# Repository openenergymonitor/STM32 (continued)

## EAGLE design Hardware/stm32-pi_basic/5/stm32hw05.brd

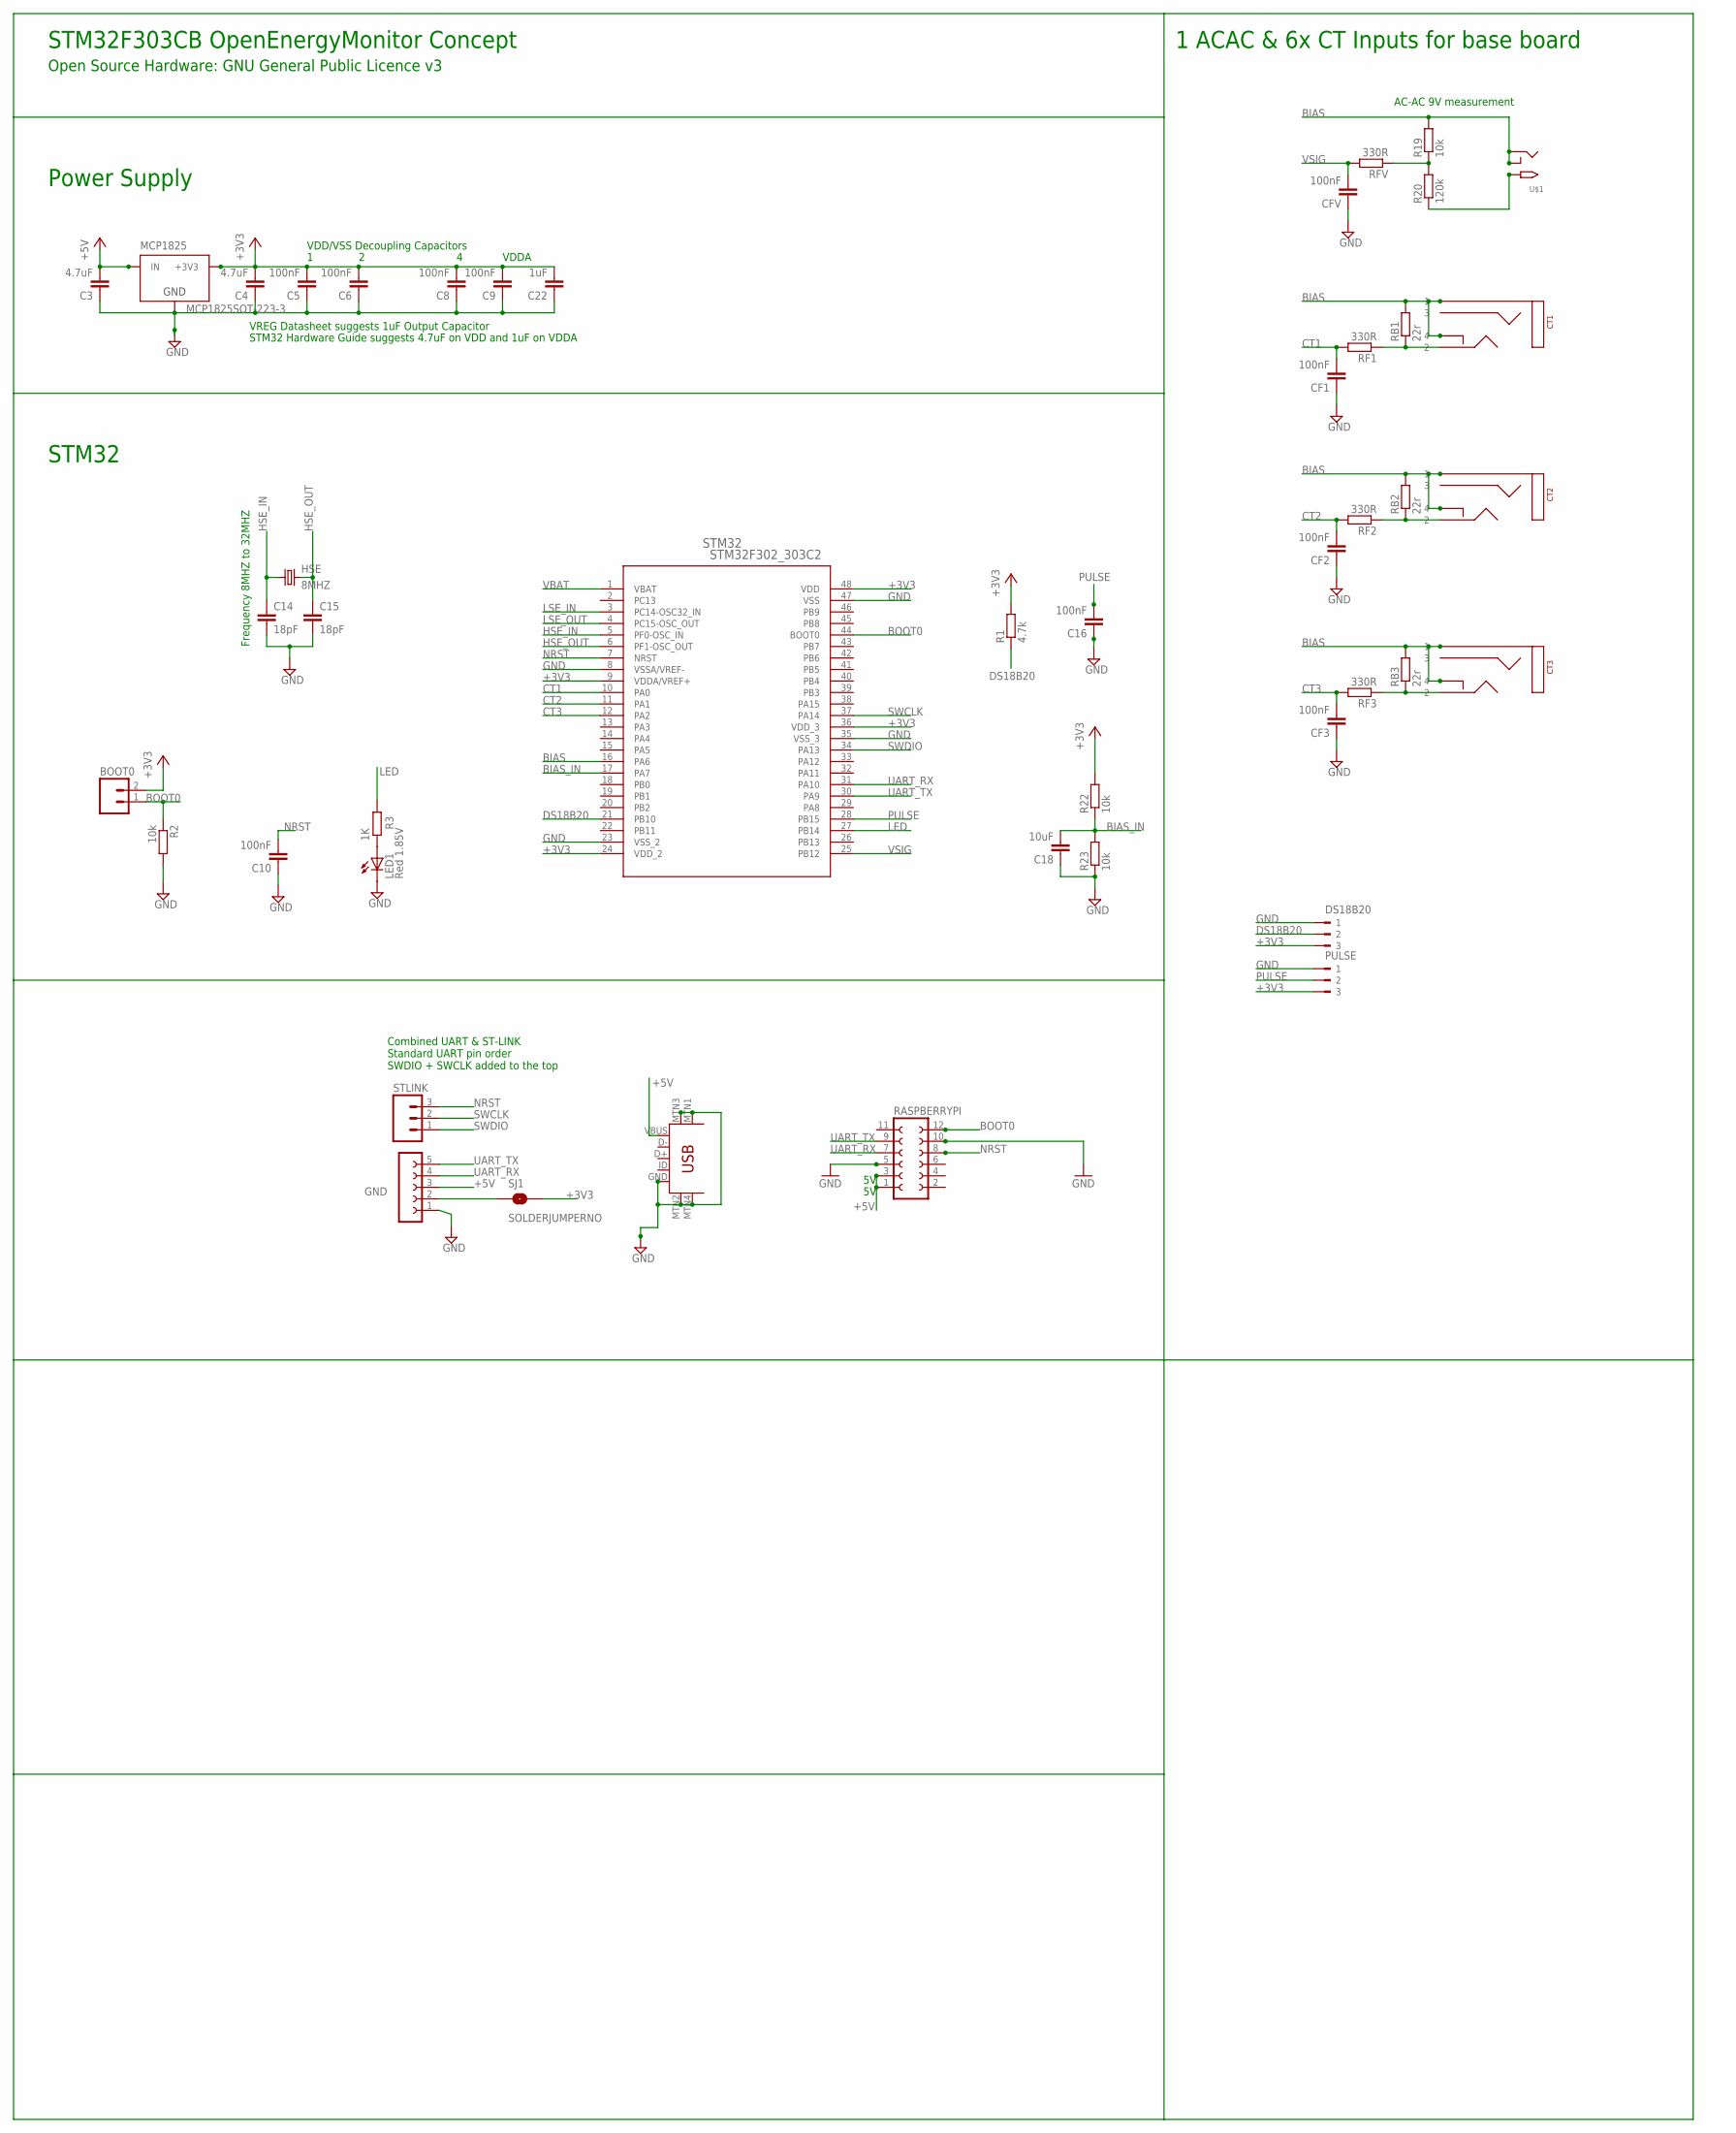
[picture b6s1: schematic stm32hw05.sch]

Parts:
BOOT0: M02PTH; 1X02
C3, C4: 4.7uF; C0603
C5, C6, C8, C9, C10, C16: 100nF; C0603
C14, C15: 18pF; C0603
C18: 10uF; C0603
C22: 1uF; C0603
CF1, CF2, CF3: 100nF; C0603
CFV: 100nF; C0603
CT1, CT2, CT3: STEREO_SMD; STEREO_SMT
DS18B20: 180-3
GND: UART; FE05-1
HSE: 8MHZ; CTS406
LED1: Red 1.85V; CHIP-LED0805
MCP1825: MCP1825SOT-223-3; SOT-223
PULSE: 180-3
R1: 4.7k; R0603
R2, R19, R22, R23: 10k; R0603
R3: 1K; R0603
R20: 120k; R0603
RASPBERRYPI: FE06-2
RB1, RB2, RB3: 22r; R0603
RF1, RF2, RF3: 330R; R0603
RFV: 330R; R0603
SJ1: SOLDERJUMPERNO; SJ_2S-NO
STLINK: M03PTH; 1X03
STM32: STM32F302_303C2; LQFP48-7X7MM
U$1: 2.1MMJACKSMT; DCJACK_2MM_SMT
U$10: USB-MINIB-5PIN; USB-MINIB-CISECO

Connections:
+3V3: BOOT0.2, C4.2, C5.2, C6.2, C8.2, C9.2, C22.2, DS18B20.3, MCP1825.3 (+3V3), PULSE.3, R1.2, R22.2, SJ1.2, STM32.9 (VDDA/VREF+), STM32.24 (VDD_2), STM32.36 (VDD_3), STM32.48 (VDD)
+5V: C3.2, GND.3, MCP1825.1 (IN), RASPBERRYPI.1, RASPBERRYPI.3, U$10.VBUS
AC: R20.1, U$1.PWR2 (TIP)
ADC0: R19.1, R20.2, RFV.1
BIAS: CT1.P$1 (1), CT1.P$4 (4), CT2.P$1 (1), CT2.P$4 (4), CT3.P$1 (1), CT3.P$4 (4), R19.2, RB1.2, RB2.2, RB3.2, STM32.16 (PA6), U$1.GND (RING), U$1.GNDBREAK (RING_SW)
BIAS_IN: C18.2, R22.1, R23.2, STM32.17 (PA7)
BOOT0: BOOT0.1, R2.1, RASPBERRYPI.12, STM32.44 (BOOT0)
CT1: CF1.2, RF1.2, STM32.10 (PA0)
CT2: CF2.2, RF2.2, STM32.11 (PA1)
CT3: CF3.2, RF3.2, STM32.12 (PA2)
DS18B20: DS18B20.2, R1.1, STM32.21 (PB10)
GND: C3.1, C4.1, C5.1, C6.1, C8.1, C9.1, C10.1, C14.2, C15.2, C16.1, C18.1, C22.1, CF1.1, CF2.1, CF3.1, CFV.1, DS18B20.1, GND.1, LED1.C, MCP1825.2 (GND), PULSE.1, R2.2, R23.1, RASPBERRYPI.5, RASPBERRYPI.10, STM32.8 (VSSA/VREF-), STM32.23 (VSS_2), STM32.35 (VSS_3), STM32.47 (VSS), U$10.GND, U$10.MTN1 (MTN2), U$10.MTN2 (MTN3), U$10.MTN3 (MTN1), U$10.MTN4
HSE_IN: C14.1, HSE.1, STM32.5 (PF0-OSC_IN)
HSE_OUT: C15.1, HSE.3 (2), STM32.6 (PF1-OSC_OUT)
LED: R3.2, STM32.27 (PB14)
LSE_IN: STM32.3 (PC14-OSC32_IN)
LSE_OUT: STM32.4 (PC15-OSC_OUT)
unnamed: GND.2, SJ1.1
unnamed: CT1.P$2 (2), RB1.1, RF1.1
unnamed: CT2.P$2 (2), RB2.1, RF2.1
unnamed: CT3.P$2 (2), RB3.1, RF3.1
unnamed: LED1.A, R3.1
NRST: C10.2, RASPBERRYPI.8, STLINK.3, STM32.7 (NRST)
PULSE: C16.2, PULSE.2, STM32.28 (PB15)
SWCLK: STLINK.2, STM32.37 (PA14)
SWDIO: STLINK.1, STM32.34 (PA13)
UART_RX: GND.4, RASPBERRYPI.7, STM32.31 (PA10)
UART_TX: GND.5, RASPBERRYPI.9, STM32.30 (PA9)
VBAT: STM32.1 (VBAT)
VSIG: CFV.2, RFV.2, STM32.25 (PB12)

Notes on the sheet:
VDD/VSS Decoupling Capacitors
VDDA
VREG Datasheet suggests 1uF Output Capacitor
STM32 Hardware Guide suggests 4.7uF on VDD and 1uF on VDDA
Combined UART & ST-LINK Standard UART pin order SWDIO + SWCLK added to the top
AC-AC 9V measurement
1 ACAC & 6x CT Inputs for base board
STM32F303CB OpenEnergyMonitor Concept
Power Supply
STM32
Open Source Hardware: GNU General Public Licence v3
Frequency 8MHZ to 32MHZ

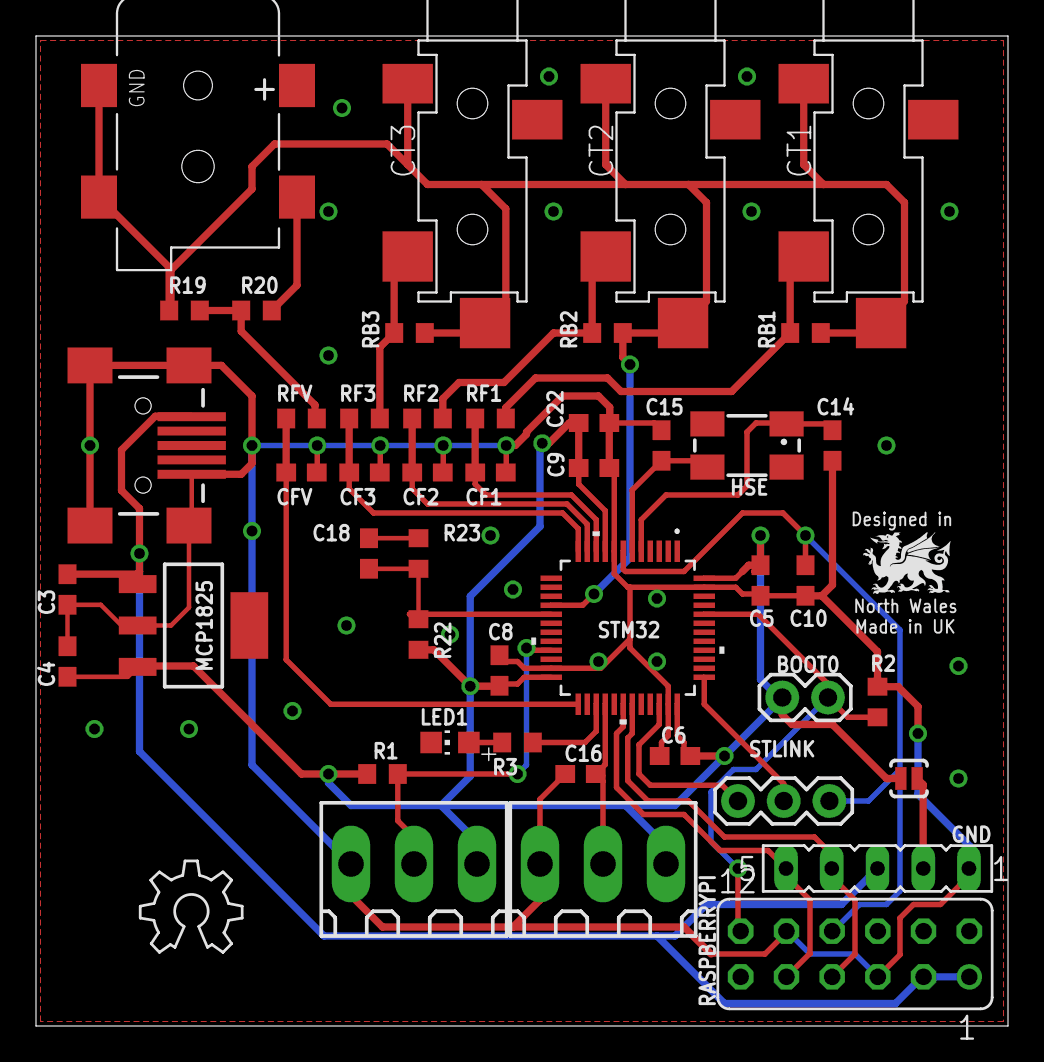
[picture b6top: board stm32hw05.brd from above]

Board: 2 copper layers, 54.0 x 55.0 mm, 47 parts (0 on the bottom side), 27 nets.

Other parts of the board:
LOGO1: OSHW_LOGO_6MILX0200-NT; OSHW_6X200_NOTEXT

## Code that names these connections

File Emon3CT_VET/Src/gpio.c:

/**
  ******************************************************************************
  * File Name          : gpio.c
  * Description        : This file provides code for the configuration
  *                      of all used GPIO pins.
  ******************************************************************************
  ** This notice applies to any and all portions of this file
  * that are not between comment pairs USER CODE BEGIN and
  * USER CODE END. Other portions of this file, whether 
  * inserted by the user or by software development tools
  * are owned by their respective copyright owners.
  *
  * COPYRIGHT(c) 2020 STMicroelectronics
  *
  * Redistribution and use in source and binary forms, with or without modification,
  * are permitted provided that the following conditions are met:
  *   1. Redistributions of source code must retain the above copyright notice,
  *      this list of conditions and the following disclaimer.
  *   2. Redistributions in binary form must reproduce the above copyright notice,
  *      this list of conditions and the following disclaimer in the documentation
  *      and/or other materials provided with the distribution.
  *   3. Neither the name of STMicroelectronics nor the names of its contributors
  *      may be used to endorse or promote products derived from this software
  *      without specific prior written permission.
  *
  * THIS SOFTWARE IS PROVIDED BY THE COPYRIGHT HOLDERS AND CONTRIBUTORS "AS IS"
  * AND ANY EXPRESS OR IMPLIED WARRANTIES, INCLUDING, BUT NOT LIMITED TO, THE
  * IMPLIED WARRANTIES OF MERCHANTABILITY AND FITNESS FOR A PARTICULAR PURPOSE ARE
  * DISCLAIMED. IN NO EVENT SHALL THE COPYRIGHT HOLDER OR CONTRIBUTORS BE LIABLE
  * FOR ANY DIRECT, INDIRECT, INCIDENTAL, SPECIAL, EXEMPLARY, OR CONSEQUENTIAL
  * DAMAGES (INCLUDING, BUT NOT LIMITED TO, PROCUREMENT OF SUBSTITUTE GOODS OR
  * SERVICES; LOSS OF USE, DATA, OR PROFITS; OR BUSINESS INTERRUPTION) HOWEVER
  * CAUSED AND ON ANY THEORY OF LIABILITY, WHETHER IN CONTRACT, STRICT LIABILITY,
  * OR TORT (INCLUDING NEGLIGENCE OR OTHERWISE) ARISING IN ANY WAY OUT OF THE USE
  * OF THIS SOFTWARE, EVEN IF ADVISED OF THE POSSIBILITY OF SUCH DAMAGE.
  *
  ******************************************************************************
  */

/* Includes ------------------------------------------------------------------*/
#include "gpio.h"
/* USER CODE BEGIN 0 */

/* USER CODE END 0 */

/*----------------------------------------------------------------------------*/
/* Configure GPIO                                                             */
/*----------------------------------------------------------------------------*/
/* USER CODE BEGIN 1 */

/* USER CODE END 1 */

/** Configure pins as 
        * Analog 
        * Input 
        * Output
        * EVENT_OUT
        * EXTI
        * Free pins are configured automatically as Analog (this feature is enabled through 
        * the Code Generation settings)
*/
void MX_GPIO_Init(void)
{

  GPIO_InitTypeDef GPIO_InitStruct;

  /* GPIO Ports Clock Enable */
  __HAL_RCC_GPIOE_CLK_ENABLE();
  __HAL_RCC_GPIOC_CLK_ENABLE();
  __HAL_RCC_GPIOF_CLK_ENABLE();
  __HAL_RCC_GPIOA_CLK_ENABLE();
  __HAL_RCC_GPIOB_CLK_ENABLE();
  __HAL_RCC_GPIOD_CLK_ENABLE();

  /*Configure GPIO pin Output Level */
  HAL_GPIO_WritePin(GPIOD, GPIO_PIN_8|GPIO_PIN_9|GPIO_PIN_10, GPIO_PIN_RESET);

  /*Configure GPIO pins : PE2 PE3 PE4 PE5 
                           PE6 PE8 PE9 PE10 
                           PE11 PE12 PE13 PE14 
                           PE15 PE0 PE1 */
  GPIO_InitStruct.Pin = GPIO_PIN_2|GPIO_PIN_3|GPIO_PIN_4|GPIO_PIN_5 
                          |GPIO_PIN_6|GPIO_PIN_8|GPIO_PIN_9|GPIO_PIN_10 
                          |GPIO_PIN_11|GPIO_PIN_12|GPIO_PIN_13|GPIO_PIN_14 
                          |GPIO_PIN_15|GPIO_PIN_0|GPIO_PIN_1;
  GPIO_InitStruct.Mode = GPIO_MODE_ANALOG;
  GPIO_InitStruct.Pull = GPIO_NOPULL;
  HAL_GPIO_Init(GPIOE, &GPIO_InitStruct);

  /*Configure GPIO pins : PC13 PC14 PC15 PC0 
                           PC1 PC2 PC3 PC4 
                           PC5 PC6 PC8 PC9 
                           PC10 PC11 PC12 */
  GPIO_InitStruct.Pin = GPIO_PIN_13|GPIO_PIN_14|GPIO_PIN_15|GPIO_PIN_0 
                          |GPIO_PIN_1|GPIO_PIN_2|GPIO_PIN_3|GPIO_PIN_4 
                          |GPIO_PIN_5|GPIO_PIN_6|GPIO_PIN_8|GPIO_PIN_9 
                          |GPIO_PIN_10|GPIO_PIN_11|GPIO_PIN_12;
  GPIO_InitStruct.Mode = GPIO_MODE_ANALOG;
  GPIO_InitStruct.Pull = GPIO_NOPULL;
  HAL_GPIO_Init(GPIOC, &GPIO_InitStruct);

  /*Configure GPIO pins : PF9 PF10 PF2 PF6 */
  GPIO_InitStruct.Pin = GPIO_PIN_9|GPIO_PIN_10|GPIO_PIN_2|GPIO_PIN_6;
  GPIO_InitStruct.Mode = GPIO_MODE_ANALOG;
  GPIO_InitStruct.Pull = GPIO_NOPULL;
  HAL_GPIO_Init(GPIOF, &GPIO_InitStruct);

  /*Configure GPIO pins : PA1 PA2 PA3 PA4 
                           PA5 PA6 PA7 PA8 
                           PA11 PA12 PA13 PA14 
                           PA15 */
  GPIO_InitStruct.Pin = GPIO_PIN_1|GPIO_PIN_2|GPIO_PIN_3|GPIO_PIN_4 
                          |GPIO_PIN_5|GPIO_PIN_6|GPIO_PIN_7|GPIO_PIN_8 
                          |GPIO_PIN_11|GPIO_PIN_12|GPIO_PIN_13|GPIO_PIN_14 
                          |GPIO_PIN_15;
  GPIO_InitStruct.Mode = GPIO_MODE_ANALOG;
  GPIO_InitStruct.Pull = GPIO_NOPULL;
  HAL_GPIO_Init(GPIOA, &GPIO_InitStruct);

  /*Configure GPIO pins : PB2 PB10 PB11 PB13 
                           PB14 PB15 PB3 PB4 
                           PB5 PB6 PB7 PB8 
                           PB9 */
  GPIO_InitStruct.Pin = GPIO_PIN_2|GPIO_PIN_10|GPIO_PIN_11|GPIO_PIN_13 
                          |GPIO_PIN_14|GPIO_PIN_15|GPIO_PIN_3|GPIO_PIN_4 
                          |GPIO_PIN_5|GPIO_PIN_6|GPIO_PIN_7|GPIO_PIN_8 
                          |GPIO_PIN_9;
  GPIO_InitStruct.Mode = GPIO_MODE_ANALOG;
  GPIO_InitStruct.Pull = GPIO_NOPULL;
  HAL_GPIO_Init(GPIOB, &GPIO_InitStruct);

  /*Configure GPIO pins : PD8 PD9 PD10 */
  GPIO_InitStruct.Pin = GPIO_PIN_8|GPIO_PIN_9|GPIO_PIN_10;
  GPIO_InitStruct.Mode = GPIO_MODE_OUTPUT_PP;
  GPIO_InitStruct.Pull = GPIO_NOPULL;
  GPIO_InitStruct.Speed = GPIO_SPEED_FREQ_LOW;
  HAL_GPIO_Init(GPIOD, &GPIO_InitStruct);

  /*Configure GPIO pins : PD12 PD13 PD14 PD15 
                           PD0 PD1 PD2 PD3 
                           PD4 PD5 PD6 PD7 */
  GPIO_InitStruct.Pin = GPIO_PIN_12|GPIO_PIN_13|GPIO_PIN_14|GPIO_PIN_15 
                          |GPIO_PIN_0|GPIO_PIN_1|GPIO_PIN_2|GPIO_PIN_3 
                          |GPIO_PIN_4|GPIO_PIN_5|GPIO_PIN_6|GPIO_PIN_7;
  GPIO_InitStruct.Mode = GPIO_MODE_ANALOG;
  GPIO_InitStruct.Pull = GPIO_NOPULL;
  HAL_GPIO_Init(GPIOD, &GPIO_InitStruct);

}

/* USER CODE BEGIN 2 */

/* USER CODE END 2 */

/**
  * @}
  */

/**
  * @}
  */

/************************ (C) COPYRIGHT STMicroelectronics *****END OF FILE****/

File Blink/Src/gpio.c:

/**
  ******************************************************************************
  * File Name          : gpio.c
  * Description        : This file provides code for the configuration
  *                      of all used GPIO pins.
  ******************************************************************************
  ** This notice applies to any and all portions of this file
  * that are not between comment pairs USER CODE BEGIN and
  * USER CODE END. Other portions of this file, whether 
  * inserted by the user or by software development tools
  * are owned by their respective copyright owners.
  *
  * COPYRIGHT(c) 2018 STMicroelectronics
  *
  * Redistribution and use in source and binary forms, with or without modification,
  * are permitted provided that the following conditions are met:
  *   1. Redistributions of source code must retain the above copyright notice,
  *      this list of conditions and the following disclaimer.
  *   2. Redistributions in binary form must reproduce the above copyright notice,
  *      this list of conditions and the following disclaimer in the documentation
  *      and/or other materials provided with the distribution.
  *   3. Neither the name of STMicroelectronics nor the names of its contributors
  *      may be used to endorse or promote products derived from this software
  *      without specific prior written permission.
  *
  * THIS SOFTWARE IS PROVIDED BY THE COPYRIGHT HOLDERS AND CONTRIBUTORS "AS IS"
  * AND ANY EXPRESS OR IMPLIED WARRANTIES, INCLUDING, BUT NOT LIMITED TO, THE
  * IMPLIED WARRANTIES OF MERCHANTABILITY AND FITNESS FOR A PARTICULAR PURPOSE ARE
  * DISCLAIMED. IN NO EVENT SHALL THE COPYRIGHT HOLDER OR CONTRIBUTORS BE LIABLE
  * FOR ANY DIRECT, INDIRECT, INCIDENTAL, SPECIAL, EXEMPLARY, OR CONSEQUENTIAL
  * DAMAGES (INCLUDING, BUT NOT LIMITED TO, PROCUREMENT OF SUBSTITUTE GOODS OR
  * SERVICES; LOSS OF USE, DATA, OR PROFITS; OR BUSINESS INTERRUPTION) HOWEVER
  * CAUSED AND ON ANY THEORY OF LIABILITY, WHETHER IN CONTRACT, STRICT LIABILITY,
  * OR TORT (INCLUDING NEGLIGENCE OR OTHERWISE) ARISING IN ANY WAY OUT OF THE USE
  * OF THIS SOFTWARE, EVEN IF ADVISED OF THE POSSIBILITY OF SUCH DAMAGE.
  *
  ******************************************************************************
  */

/* Includes ------------------------------------------------------------------*/
#include "gpio.h"
/* USER CODE BEGIN 0 */

/* USER CODE END 0 */

/*----------------------------------------------------------------------------*/
/* Configure GPIO                                                             */
/*----------------------------------------------------------------------------*/
/* USER CODE BEGIN 1 */

/* USER CODE END 1 */

/** Configure pins as 
        * Analog 
        * Input 
        * Output
        * EVENT_OUT
        * EXTI
        * Free pins are configured automatically as Analog (this feature is enabled through 
        * the Code Generation settings)
*/
void MX_GPIO_Init(void)
{

  GPIO_InitTypeDef GPIO_InitStruct;

  /* GPIO Ports Clock Enable */
  __HAL_RCC_GPIOC_CLK_ENABLE();
  __HAL_RCC_GPIOF_CLK_ENABLE();
  __HAL_RCC_GPIOA_CLK_ENABLE();
  __HAL_RCC_GPIOB_CLK_ENABLE();
  __HAL_RCC_GPIOD_CLK_ENABLE();

  /*Configure GPIO pin Output Level */
  HAL_GPIO_WritePin(GPIOA, GPIO_PIN_5, GPIO_PIN_RESET);

  /*Configure GPIO pins : PC13 PC14 PC15 PC0 
                           PC1 PC2 PC3 PC4 
                           PC5 PC6 PC7 PC8 
                           PC9 PC10 PC11 PC12 */
  GPIO_InitStruct.Pin = GPIO_PIN_13|GPIO_PIN_14|GPIO_PIN_15|GPIO_PIN_0 
                          |GPIO_PIN_1|GPIO_PIN_2|GPIO_PIN_3|GPIO_PIN_4 
                          |GPIO_PIN_5|GPIO_PIN_6|GPIO_PIN_7|GPIO_PIN_8 
                          |GPIO_PIN_9|GPIO_PIN_10|GPIO_PIN_11|GPIO_PIN_12;
  GPIO_InitStruct.Mode = GPIO_MODE_ANALOG;
  GPIO_InitStruct.Pull = GPIO_NOPULL;
  HAL_GPIO_Init(GPIOC, &GPIO_InitStruct);

  /*Configure GPIO pins : PF0 PF1 */
  GPIO_InitStruct.Pin = GPIO_PIN_0|GPIO_PIN_1;
  GPIO_InitStruct.Mode = GPIO_MODE_ANALOG;
  GPIO_InitStruct.Pull = GPIO_NOPULL;
  HAL_GPIO_Init(GPIOF, &GPIO_InitStruct);

  /*Configure GPIO pins : PA0 PA1 PA2 PA3 
                           PA4 PA6 PA7 PA8 
                           PA9 PA10 PA11 PA12 
                           PA13 PA14 PA15 */
  GPIO_InitStruct.Pin = GPIO_PIN_0|GPIO_PIN_1|GPIO_PIN_2|GPIO_PIN_3 
                          |GPIO_PIN_4|GPIO_PIN_6|GPIO_PIN_7|GPIO_PIN_8 
                          |GPIO_PIN_9|GPIO_PIN_10|GPIO_PIN_11|GPIO_PIN_12 
                          |GPIO_PIN_13|GPIO_PIN_14|GPIO_PIN_15;
  GPIO_InitStruct.Mode = GPIO_MODE_ANALOG;
  GPIO_InitStruct.Pull = GPIO_NOPULL;
  HAL_GPIO_Init(GPIOA, &GPIO_InitStruct);

  /*Configure GPIO pin : PA5 */
  GPIO_InitStruct.Pin = GPIO_PIN_5;
  GPIO_InitStruct.Mode = GPIO_MODE_OUTPUT_PP;
  GPIO_InitStruct.Pull = GPIO_NOPULL;
  GPIO_InitStruct.Speed = GPIO_SPEED_FREQ_LOW;
  HAL_GPIO_Init(GPIOA, &GPIO_InitStruct);

  /*Configure GPIO pins : PB0 PB1 PB2 PB10 
                           PB11 PB12 PB13 PB14 
                           PB15 PB3 PB4 PB5 
                           PB6 PB7 PB8 PB9 */
  GPIO_InitStruct.Pin = GPIO_PIN_0|GPIO_PIN_1|GPIO_PIN_2|GPIO_PIN_10 
                          |GPIO_PIN_11|GPIO_PIN_12|GPIO_PIN_13|GPIO_PIN_14 
                          |GPIO_PIN_15|GPIO_PIN_3|GPIO_PIN_4|GPIO_PIN_5 
                          |GPIO_PIN_6|GPIO_PIN_7|GPIO_PIN_8|GPIO_PIN_9;
  GPIO_InitStruct.Mode = GPIO_MODE_ANALOG;
  GPIO_InitStruct.Pull = GPIO_NOPULL;
  HAL_GPIO_Init(GPIOB, &GPIO_InitStruct);

  /*Configure GPIO pin : PD2 */
  GPIO_InitStruct.Pin = GPIO_PIN_2;
  GPIO_InitStruct.Mode = GPIO_MODE_ANALOG;
  GPIO_InitStruct.Pull = GPIO_NOPULL;
  HAL_GPIO_Init(GPIOD, &GPIO_InitStruct);

}

/* USER CODE BEGIN 2 */

/* USER CODE END 2 */

/**
  * @}
  */

/**
  * @}
  */

/************************ (C) COPYRIGHT STMicroelectronics *****END OF FILE****/

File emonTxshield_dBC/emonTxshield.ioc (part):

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Mcu.Name=STM32F303R(D-E)Tx
Mcu.Package=LQFP64
Mcu.UserName=STM32F303RETx
PA0.Mode=IN1-Single-Ended
PA0.Signal=ADC1_IN1
PA1.GPIOParameters=GPIO_Label
PA1.GPIO_Label=ADC1_IN2(CT2.1)
PA1.Mode=IN2-Single-Ended
PA1.Signal=ADC1_IN2
PA13.GPIOParameters=GPIO_Label
PA13.GPIO_Label=TMS
PA13.Mode=Serial_Wire
PA13.Signal=SYS_JTMS-SWDIO
PA14.GPIOParameters=GPIO_Label
PA14.GPIO_Label=TCK
PA14.Mode=Serial_Wire
PA14.Signal=SYS_JTCK-SWCLK
PA2.GPIOParameters=GPIO_Speed,GPIO_PuPd,GPIO_Label,GPIO_Mode
PA2.GPIO_Label=USART_TX
PA2.GPIO_Mode=GPIO_MODE_AF_PP
PA2.GPIO_PuPd=GPIO_NOPULL
PA2.GPIO_Speed=GPIO_SPEED_FREQ_LOW
PA2.Mode=Asynchronous
PA2.Signal=USART2_TX
PA3.GPIOParameters=GPIO_Speed,GPIO_PuPd,GPIO_Label,GPIO_Mode
PA3.GPIO_Label=USART_RX
PA3.GPIO_Mode=GPIO_MODE_AF_PP
PA3.GPIO_PuPd=GPIO_NOPULL
PA3.GPIO_Speed=GPIO_SPEED_FREQ_LOW
PA3.Mode=Asynchronous
PA3.Signal=USART2_RX
PA4.GPIOParameters=GPIO_Label
PA4.GPIO_Label=ADC2_IN1 (CT2.2)
PA4.Mode=IN1-Single-Ended
PA4.Signal=ADC2_IN1
PA5.GPIOParameters=GPIO_Speed,GPIO_PuPd,GPIO_Label,GPIO_Mode
PA5.GPIO_Label=LD2 [Green Led]
PA5.GPIO_Mode=GPIO_MODE_OUTPUT_PP
PA5.GPIO_PuPd=GPIO_NOPULL
PA5.GPIO_Speed=GPIO_SPEED_FREQ_LOW
PA5.Signal=GPIO_Output
PA6.Mode=Follower
PA6.Signal=OPAMP2_VOUT
PA7.Mode=Follower
PA7.Signal=OPAMP2_VINP
PA9.GPIOParameters=GPIO_PuPd,GPIO_Label
PA9.GPIO_Label=OneWire_1
PA9.GPIO_PuPd=GPIO_NOPULL
PA9.Mode=Half_duplex(single_wire_mode)
PA9.Signal=USART1_TX
PB0.GPIOParameters=GPIO_Label
PB0.GPIO_Label=ADC3_IN12(CT2.3)
PB0.Mode=IN12-Single-Ended
PB0.Signal=ADC3_IN12
PB1.Mode=IN1-Single-Ended
PB1.Signal=ADC3_IN1
PB10.GPIOParameters=GPIO_PuPd,GPIO_Label
PB10.GPIO_Label=OneWire_2
PB10.GPIO_PuPd=GPIO_NOPULL
PB10.Mode=Half_duplex(single_wire_mode)
PB10.Signal=USART3_TX
PB11.Mode=IN14-Single-Ended
PB11.Signal=ADC1_IN14
PB12.GPIOParameters=GPIO_Label
PB12.GPIO_Label=VT1
PB12.Mode=IN3-Single-Ended
PB12.Signal=ADC4_IN3
PB13.Mode=IN5-Single-Ended
PB13.Signal=ADC3_IN5
PB14.GPIOParameters=GPIO_Label
PB14.GPIO_Label=VT2
PB14.Mode=IN4-Single-Ended
PB14.Signal=ADC4_IN4
PB15.GPIOParameters=GPIO_Label
PB15.GPIO_Label=VT3
PB15.Mode=IN5-Single-Ended
PB15.Signal=ADC4_IN5
PB2.Mode=IN12-Single-Ended
PB2.Signal=ADC2_IN12
PB3.GPIOParameters=GPIO_Label
PB3.GPIO_Label=SWO
PB3.Signal=SYS_JTDO-TRACESWO
PC0.Signal=ADCx_IN6
PC1.GPIOParameters=GPIO_Label
PC1.GPIO_Label=ADC2_IN7 (CT2.4)
PC1.Signal=ADCx_IN7
PC13.GPIOParameters=GPIO_Label,GPIO_ModeDefaultEXTI
PC13.GPIO_Label=B1 [Blue PushButton]
PC13.GPIO_ModeDefaultEXTI=GPIO_MODE_IT_FALLING
PC13.Signal=GPXTI13
PC14-OSC32_IN.Mode=LSE-External-Oscillator
PC14-OSC32_IN.Signal=RCC_OSC32_IN
PC15-OSC32_OUT.Mode=LSE-External-Oscillator
PC15-OSC32_OUT.Signal=RCC_OSC32_OUT
PC2.Signal=ADCx_IN8
PC3.Signal=ADCx_IN9
PC4.Mode=IN5-Single-Ended
PC4.Signal=ADC2_IN5
PC7.GPIOParameters=GPIO_Label
PC7.GPIO_Label=ADC_TRIG
PC7.Signal=S_TIM8_CH2
PF0-OSC_IN.Mode=HSE-External-Clock-Source
PF0-OSC_IN.Signal=RCC_OSC_IN
PF1-OSC_OUT.Signal=RCC_OSC_OUT
RCC.HSE_VALUE=8000000
RCC.SYSCLKFreq_VALUE=72000000
RCC.SYSCLKSourceVirtual=RCC_SYSCLKSOURCE_PLLCLK
board=NUCLEO-F303RE
boardIOC=true

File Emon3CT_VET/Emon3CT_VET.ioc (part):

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Mcu.Name=STM32F303V(D-E)Tx
Mcu.Package=LQFP100
Mcu.UserName=STM32F303VETx
PA0.Mode=IN1-Single-Ended
PA0.Signal=ADC1_IN1
PA10.Mode=Asynchronous
PA10.Signal=USART1_RX
PA9.Mode=Asynchronous
PA9.Signal=USART1_TX
PB0.Mode=IN12-Single-Ended
PB0.Signal=ADC3_IN12
PB1.Mode=IN1-Single-Ended
PB1.Signal=ADC3_IN1
PB12.Mode=Follower
PB12.Signal=OPAMP4_VOUT
PC7.Signal=S_TIM8_CH2
PD10.Signal=GPIO_Output
PD11.Mode=Follower
PD11.Signal=OPAMP4_VINP
PD8.Signal=GPIO_Output
PD9.Signal=GPIO_Output
PE7.Mode=IN13-Single-Ended
PE7.Signal=ADC3_IN13
PF0-OSC_IN.Mode=HSE-External-Oscillator
PF0-OSC_IN.Signal=RCC_OSC_IN
PF1-OSC_OUT.Mode=HSE-External-Oscillator
PF1-OSC_OUT.Signal=RCC_OSC_OUT
RCC.HSE_VALUE=8000000
RCC.SYSCLKFreq_VALUE=72000000
RCC.SYSCLKSourceVirtual=RCC_SYSCLKSOURCE_PLLCLK
board=custom

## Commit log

2018-03-17 OEM ADC Demo 1.0 thanks to @dBC
2018-03-17 makefile
2018-03-17 readme
2018-03-21 STM32F303
2018-03-21 user code
2018-03-24 dBC txshield demo
2018-03-25 add platformio.ini to test
2018-03-25 calculate rms voltage and current
2018-03-25 power calculation
2018-03-25 print floats
2018-03-26 .mak files
2018-03-26 add working platfomrio.ini
2018-03-26 add std=gnu99 pio build flag
2018-03-29 remove sudo
2018-04-04 copy of STM02
2018-04-04 parallel sampling of ADC1 and ADC2, zero crossing detection for power calculation
2018-04-05 timer8 trigger attempt
2018-04-05 timer8 trigger
2018-10-05 Blink example
2018-10-05 make and platformio example for blink
2018-10-05 p1 of blink guide
2018-10-05 blink tutorial
2018-10-05 serial output example
2018-10-06 serial notes
2018-10-07 basic analog read examples
2018-10-07 adc example 3
2018-10-07 interrupt example
2018-10-07 minor
2018-10-07 ADC example
2018-10-07 DMA example
2018-10-07 source links
2018-10-07 Emon example
2018-10-08 working single channel emontx shield example
2018-10-09 example with voltage and current measurement on seperate ADC's
2018-10-09 docs
2018-10-09 img path
2018-10-09 list of firmware examples
2018-10-09 st-link
2018-10-09 stlink
2018-10-09 st-link notes
2018-10-09 uart upload
2018-10-09 bluepillblink
2018-10-09 first hw design
2018-10-10 opamp voltage follower & anti-alias prototype
2018-10-11 scope pics
2018-10-11 move floating point math out of ISR
2018-10-11 Emon3 example with offset removal thanks to @Robert.Wall
2018-10-12 code clean up
2018-10-12 count full cycles rather than half cycles
2018-10-12 1CT and 3CT examples
2018-10-12 rename examples
2018-10-13 rev3
2018-10-15 STM Duino guides
2018-10-15 shield modifications
2018-10-15 latest example from @dBC
2018-10-16 fix missing c99 flag in platformio.ini
2018-10-31 rpi upload example
2018-10-31 rpiautoupload
2018-11-20 attempt at ds18b20 support (not working)
2018-11-22 working ds18b20 example
2018-11-22 fixed from STM32CubeMX, working example
2018-11-22 pulse counting
2018-11-23 stm32 notes and design 4
2018-11-23 merged image
2018-11-23 programming section
2018-11-23 image
2018-11-28 v5 design
2018-11-28 gerbers
2018-11-28 tented vias
2018-11-28 board pic
2018-11-29 added NRST & 3.3v routing
2018-12-05 move UART to PA9 & PA10, move pulse, LED & ds18b20
2018-12-05 updated board screenshot
2019-01-08 examples for STM32F303CBT6
2019-01-08 compiled
2019-01-08 includes DS18B20 and pulse count
2019-01-08 latest
2019-01-08 compile
2019-01-14 add platformIO support for STM32F303CB
2019-01-15 add mockup board
2019-01-30 RFM69 test code
    working on STM32F303RE Nucleo
    thanks to @cristi85
    https://github.com/cristi85/RFM69
2019-01-31 STM32 Tx / Rx Tests Working
    Included also, arduino / atmega compatible sketches for testing.
2019-02-04 EmonCT_RFM69 Working
    In the Makefile, compiler optimisation flag needed to be set to -Og.
    Cube will revert it to the default of -O3 upon new code generation
2019-02-05 RFM69 update
2019-02-05 RFM69 fix
2019-02-07 change default power level
    to protect rfm69 modules
2019-05-22 v0.1 large stm board
2019-05-27 commit v0.2
2019-05-30 v0.3
2019-06-05 v0.3 and notes
2019-06-11 v0.3a and gerbers
    also includes prelim cubeMX project
2019-06-18 doco update
2019-06-27 v0.4 update
2019-06-28 v0.4 update
    checked
2019-07-14 v0.5
    changed drill hole size from .35mm to .5mm
2019-07-29 commit BoM v0.5
2019-08-10 reorganise Hardware folder.
2019-08-10 doco update
    st-util to flash virgin chip
2019-08-10 update doco
2019-08-10 hardware changes
2019-08-23 reorganise files and upload v0.6 brd
2019-09-08 commit SPI tests
2019-10-03 UART DMA stm32
2019-10-11 commit IT method UART receive
2019-10-16 DMA UART hack
2019-10-22 adc retest
2019-10-26 SPI tests
2019-10-29 commit 3CT example
2019-11-04 First working MBUS example
2019-11-09 commit JSON parser and arm_math examples
2019-11-25 update, plus reports
2019-12-06 board v0.7
2019-12-15 update dec2019
    v0.7 gerbers sent to manf.
2019-12-15 cleanup
2020-01-29 hz measurement commit
2020-02-06 rPi_RFM additions
2020-02-13 commit
    RFM69
    PULSE input
    started on bringing in ds18b20 code from dBC's work.
2020-02-29 minor commit
2020-03-22 commit, PF hunting start
2020-03-26 fixed cycle count problem in working4
2020-03-26 fix extra cycle count in main.c
    last_positive_V was getting cleared by memset, thus, on the next set of readings a cycle would immediately get counted. threw the Hz calc error off by about 0.1 Hz.
2020-03-26 Update main.c
    corrected the cycle = true for cycle counting. now getting 50Hz readings exactly.
    first draft of phase_corrections..
2020-03-26 Update main.c
    phase_correctors working?
2020-03-27 tidy
2020-04-06 working4 to use internal oscillator
    just debugging something
2020-04-10 Emon3CT Example for STM32F303VET used on STM32-pi-full v0.7
2020-04-10 stm32 pi learning firmware
2020-04-10 move process_frame out of callback
2020-04-11 making sure the dma counter is such that we have 'future' samples
2020-04-11 Improved math and higher sample frequency
2020-04-14 move examples to software
2020-04-14 simplify gitignore
2020-04-14 remove duplicates
2020-04-14 add stm32 pi notes
2020-04-14 minor changes in docs
2020-04-14 Include copy of original Emon3CT_CB, revert BlinkCB to be basic blink
2020-04-14 Automatic phase correction based on Dan Bates's shifting voltage array approach
2020-04-14 phase correction approach based on Robert Wall's EmonLibCM method
2020-04-14 update links to software
2020-04-14 link to all examples
2020-04-14 hardware links
2020-04-14 rising/falling edge trigger not working
2020-04-15 Update main.c
    find mode in set of phase_corrections[] value at moment of direction change.
2020-04-18 phase correction tested, seems to work!
    buffer index shifting, maximum PF hunting, modal value
2020-04-18 setting rising / falling edges of adc1 & adc3
    this default setting is logical for the typical phase errors found in our equipment.
    I've set a usecs lag of 95usec in adc.c as a default value until something better than a kettle is used for phase correction :+1: .
2020-04-19 EEPROM emulation tested and working.
    and also added a clearer confidence indication of the mode value returned from the PF hunt result array.
2020-04-20 hardware rtc working, with serial commands also
    Get time by sending string "{G:RTC}"
    Set time by sending "{S:RTC:1587405808}" for example.
    https://www.epochconverter.com/
2020-05-24 update, minor board revision
2020-05-28 non-Blocking UART transmissions
    Saving 40ms at 460800 baud or 160ms at 115200 baud.
    Now takes less than a millisecond to begin the UART transmit, happens in the background.
    notes included on how to fire UART transmissions consequtively withing messing up the buffer or dropping transmissions.
2020-05-28 minor, uipdate BoMs
2020-06-02 minor changes, some checks on proto v0.8 done.
2020-06-04 Various checks.
2020-06-10 backup various changes
    JSON parser tidy
    RESET CAUSE reported, and reset counter in RTC backup RAM.
    RFM69 Implementation improvements: removed annecessary SPI transactions while waiting for a Rx.
2020-06-23 3-phase gen
2020-06-23 DAC 3-phase gen working
2020-07-12 v0.9 backup
2020-07-13 v0.9 for checking
    update PCB and enclosure
2020-07-16 v0.9a update
2020-07-19 v0.9b
2020-07-21 Migrate EmonCT3
2020-07-22 bias changed to inverting op-amp with in-the-loop compensator
2020-08-04 update readme.md
    including link for the enclosure CAD
2020-08-14 backup on a dodgey laptop
2020-08-18 commit v1.0
2020-08-19 UART Tx improvments and v1.0 HW change
2020-08-21 commit v1.0 HW for prototype.
2020-08-21 correct rotation of p&p'd parts.
2020-09-15 update ac-ac resistor value for new vref
2020-09-29 modified: Software/Sombrero_VE_Working6/Makefile modified: Software/Sombrero_VE_Working6/Src/RFM69.c modified: Software/Sombrero_VE_Working6/Src/RFM69_ext.c modified: Software/Sombrero_VE_Working6/Sr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
2020-10-05 changed lmv824 3-phase feedback resistor values
2020-10-06 modified: Hardware/stm32-pi_full/stm32 v1.1 working BoM/JLCSMT_Sample_BOM1.xlsx modified: Hardware/stm32-pi_full/stm32 v1.1.brd modified: Hardware/stm32-pi_full/stm32 v1.1.sch modified: Software/Somb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
2020-10-06 MPNs updated
2020-10-06 changes results calculation method
    making room now to be able to update phase corrections at higher resolution in time. i.e. if a load come on which subjects the CT to a different phase error, it'll be able to react quicker.
    more to implement until it's working...
2020-10-06 move UART header back away from case edge
2020-10-12 pulse detect fix. separated readings timer and posting timer implemented.
2020-10-13 improved zero crossing detection
2020-10-13 latest build using STM32CubeMX
2020-10-13 Code for measuring phase angle between voltage and current inputs
2020-10-23 modified: Hardware/stm32-pi_full/stm32 v1.2.brd modified: Hardware/stm32-pi_full/stm32 v1.2.sch modified: Software/Sombrero_VE_Working6/build/Sombrero_VE_Working6.bin
2020-10-26 brd changes
2020-10-30 test1
2020-10-31 DIO1 pin enable and routing for LoRaWAN rfm9x modules.
2020-11-11 code refactor begin, rpi script update
2020-11-14 sync
2020-11-18 modified: Hardware/stm32-pi_basic/6/stm32hw06.brd modified: Hardware/stm32-pi_full/stm32 v1.1.brd deleted: Protecting Inputs in Digital Electronics ESD Protection | DigiKey.pdf
2020-11-20 new file: Hardware/stm32-pi_basic/6/dxfimp.scr new file: Hardware/stm32-pi_basic/6/stm32hw06_.brd new file: Hardware/stm32-pi_basic/6/stm32hw06_.sch new file: literature/Protecting Inputs in Digital 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
2020-11-20 deleted: Hardware/stm32-pi_basic/6/dxfimp.scr modified: Hardware/stm32-pi_basic/6/stm32hw06.brd modified: Hardware/stm32-pi_basic/6/stm32hw06.sch
2020-11-23 sync mini v0.2
2021-01-02 Added F303VC variant
2021-01-18 reorganise
2021-01-19 sync code for stm32mini
2021-01-19 sync add files. stm32mini working
2021-01-22 sync, raido tested
2021-02-13 added spice model
2021-02-25 sync doco
2021-03-02 update spice model
2021-03-16 enclosure files added
2021-03-16 enclosure notes
2021-04-09 Example of receiving data using Jeelib based RF69 Native driver
2021-04-09 moved STM32_RF69 example
2021-04-09 STM32 max rf69n example
2021-04-16 fix issue with rf69n serial print
